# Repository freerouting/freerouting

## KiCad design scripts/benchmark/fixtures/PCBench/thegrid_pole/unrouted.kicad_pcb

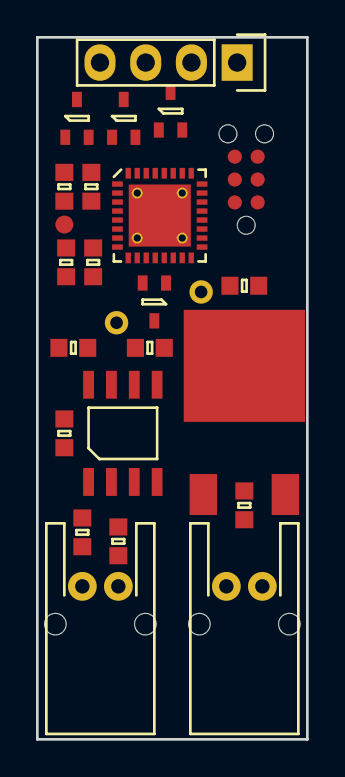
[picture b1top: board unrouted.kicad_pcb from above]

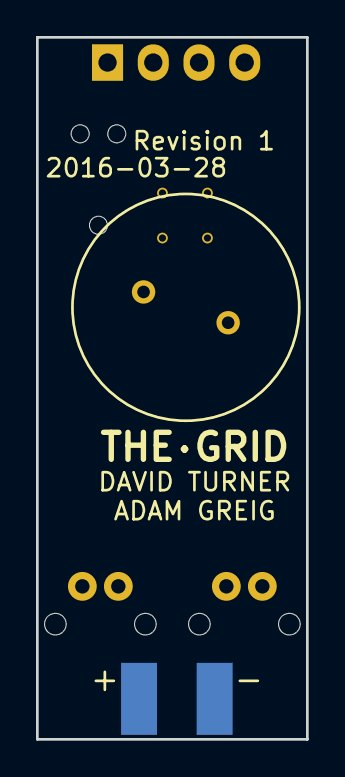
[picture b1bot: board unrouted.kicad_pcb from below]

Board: 2 copper layers, 15.0 x 39.0 mm, 25 parts (2 on the bottom side), 18 nets, no tracks yet.

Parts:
C1, C3, C5, C6: 100n; 0603
C2: 4u7; 0603
C4: 10n; 0603
C7: 10u; 0603
C8: 1u; 0603
IC1: LMx93; SOIC-8
IC2: STM32F0xxKxUx; QFN-32-EP-ST
P1: POWER_IN; minipow_edge
P2: BUS_IN; S02B-PASK-2
P3: BUS_OUT; S02B-PASK-2
P4: SWD_TC; TC2030-NL
P5: LEDs; Pin_Header_Straight_1x04
Q1, Q2, Q3, Q4: MTM232270LBF; SOT-323
R1, R2: 10k; 0603
R3: 1M; 0603
SP1: SPEAKER; piezo
TP1: RST; TESTPAD
U1: LD1117S33TR; TO-252-3

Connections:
+3V3: C1.2, C2.1, C3.1, C4.1, C5.1, C7.1, C8.1, IC1.8, IC2.1, IC2.5, IC2.17, P4.1, R1.1, U1.2
+12V: C6.1, P1.2, P5.1, SP1.1, U1.3
/BUS: IC1.1, IC2.9, R1.2, R3.1
/BUS_A: IC1.2, P2.1, P3.1
/BUS_B: P2.2, P3.2, R2.2
/DRIVE_B: P5.4, Q3.3
/DRIVE_G: P5.3, Q2.3
/DRIVE_R: P5.2, Q1.3
/LED_B: IC2.20, Q3.1
/LED_G: IC2.19, Q2.1
/LED_R: IC2.18, Q1.1
/PIEZO: IC2.10, Q4.1
/SWDCLK: IC2.24, P4.4
/SWDIO: IC2.23, P4.2
GND: C1.1, C2.2, C3.2, C4.2, C5.2, C6.2, C7.2, C8.2, IC1.4, IC1.5, IC1.6, IC2.31, IC2.EP, P1.1, P4.5, Q1.2, Q2.2, Q3.2, Q4.2, U1.1
unnamed: IC1.3, R2.1, R3.2
unnamed: IC2.4, TP1.1
unnamed: Q4.3, SP1.2

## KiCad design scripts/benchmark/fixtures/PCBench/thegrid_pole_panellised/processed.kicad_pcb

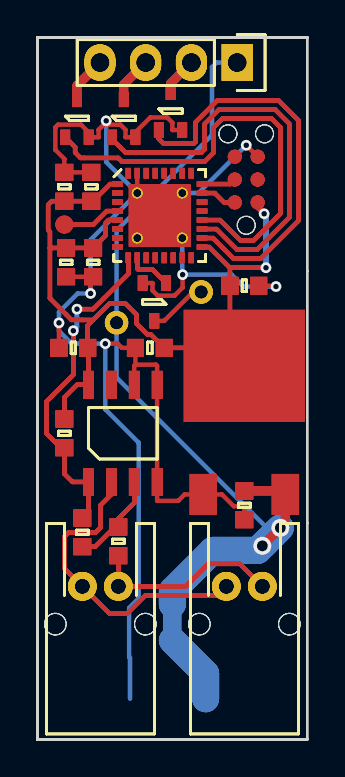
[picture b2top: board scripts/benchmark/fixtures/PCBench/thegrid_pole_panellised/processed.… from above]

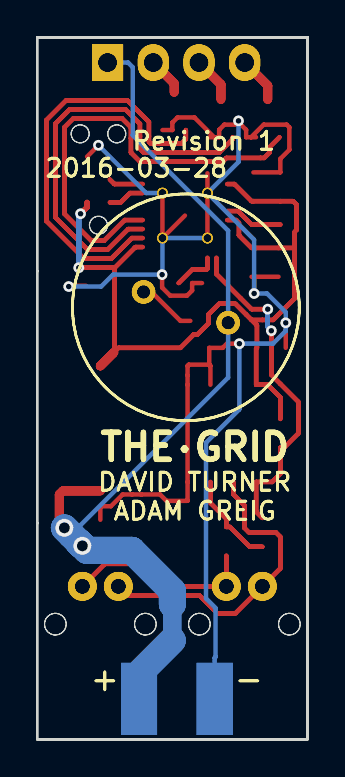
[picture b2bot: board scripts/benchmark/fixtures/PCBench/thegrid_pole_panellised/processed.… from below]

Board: 2 copper layers, 15.0 x 39.0 mm, 50 parts (4 on the bottom side), 18 nets.

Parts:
C1, C1_2, C3, C3_2, C5, C5_2, C6, C6_2: 100n; 0603
C2, C2_2: 4u7; 0603
C4, C4_2: 10n; 0603
C7, C7_2: 10u; 0603
C8, C8_2: 1u; 0603
IC1, IC1_2: LMx93; SOIC-8
IC2, IC2_2: STM32F0xxKxUx; QFN-32-EP-ST
P1, P1_2: POWER_IN; minipow_edge
P2, P2_2: BUS_IN; S02B-PASK-2
P3, P3_2: BUS_OUT; S02B-PASK-2
P4, P4_2: SWD_TC; TC2030-NL
P5, P5_2: LEDs; Pin_Header_Straight_1x04
Q1, Q1_2, Q2, Q2_2, Q3, Q3_2, Q4, Q4_2: MTM232270LBF; SOT-323
R1, R1_2, R2, R2_2: 10k; 0603
R3, R3_2: 1M; 0603
SP1, SP1_2: SPEAKER; piezo
TP1, TP1_2: RST; TESTPAD
U1, U1_2: LD1117S33TR; TO-252-3

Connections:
+3V3: C1.2, C1_2.2, C2.1, C2_2.1, C3.1, C3_2.1, C4.1, C4_2.1, C5.1, C5_2.1, C7.1, C7_2.1, C8.1, C8_2.1, IC1.8, IC1_2.8, IC2.1, IC2.5, IC2.17, IC2_2.1, IC2_2.5, IC2_2.17, P4.1, P4_2.1, R1.1, R1_2.1, U1.2, U1_2.2
+12V: C6.1, C6_2.1, P1.2, P1_2.2, P5.1, P5_2.1, SP1.1, SP1_2.1, U1.3, U1_2.3
/BUS: IC1.1, IC1_2.1, IC2.9, IC2_2.9, R1.2, R1_2.2, R3.1, R3_2.1
/BUS_A: IC1.2, IC1_2.2, P2.1, P2_2.1, P3.1, P3_2.1
/BUS_B: P2.2, P2_2.2, P3.2, P3_2.2, R2.2, R2_2.2
/DRIVE_B: P5.4, P5_2.4, Q3.3, Q3_2.3
/DRIVE_G: P5.3, P5_2.3, Q2.3, Q2_2.3
/DRIVE_R: P5.2, P5_2.2, Q1.3, Q1_2.3
/LED_B: IC2.20, IC2_2.20, Q3.1, Q3_2.1
/LED_G: IC2.19, IC2_2.19, Q2.1, Q2_2.1
/LED_R: IC2.18, IC2_2.18, Q1.1, Q1_2.1
/PIEZO: IC2.10, IC2_2.10, Q4.1, Q4_2.1
/SWDCLK: IC2.24, IC2_2.24, P4.4, P4_2.4
/SWDIO: IC2.23, IC2_2.23, P4.2, P4_2.2
GND: C1.1, C1_2.1, C2.2, C2_2.2, C3.2, C3_2.2, C4.2, C4_2.2, C5.2, C5_2.2, C6.2, C6_2.2, C7.2, C7_2.2, C8.2, C8_2.2, IC1.4, IC1.5, IC1.6, IC1_2.4, IC1_2.5, IC1_2.6, IC2.31, IC2.EP, IC2_2.31, IC2_2.EP, P1.1, P1_2.1, P4.5, P4_2.5, Q1.2, Q1_2.2, Q2.2, Q2_2.2, Q3.2, Q3_2.2, Q4.2, Q4_2.2, U1.1, U1_2.1
unnamed: IC1.3, IC1_2.3, R2.1, R2_2.1, R3.2, R3_2.2
unnamed: IC2.4, IC2_2.4, TP1.1, TP1_2.1
unnamed: Q4.3, Q4_2.3, SP1.2, SP1_2.2

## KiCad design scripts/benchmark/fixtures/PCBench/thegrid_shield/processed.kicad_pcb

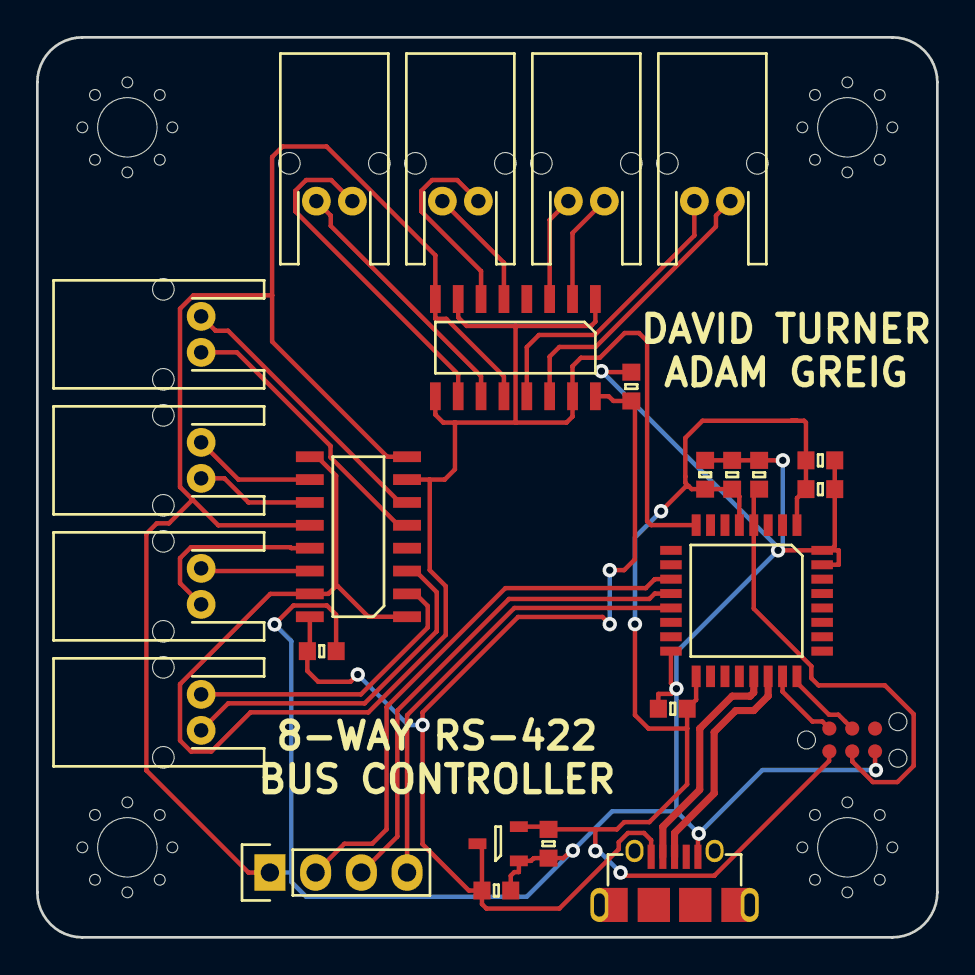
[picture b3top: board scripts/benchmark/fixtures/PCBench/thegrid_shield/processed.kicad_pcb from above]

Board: 2 copper layers, 50.0 x 50.0 mm, 29 parts (0 on the bottom side), 28 nets.

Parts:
C1, C2, C3, C6, C8: 100n; 0603
C4: 10u; 0603
C5: C; 0603
C7, C9, C10: 1u; 0603
IC1: STM32F0xxKxTx; LQFP-32
IC2: MCP1700; SOT-23
IC3, IC4: AM26C31; SOIC-16
J1: MICROUSB; MICROUSB_MOLEX_47589-0001
P1: SWD_TC; TC2030-NL
P5: SHIFT; Pin_Header_Straight_1x04
P6: BUS1; S02B-PASK-2
P7: BUS2; S02B-PASK-2
P8: BUS3; S02B-PASK-2
P9: BUS4; S02B-PASK-2
P10: BUS5; S02B-PASK-2
P11: BUS6; S02B-PASK-2
P12: BUS7; S02B-PASK-2
P13: BUS8; S02B-PASK-2
X1, X2, X3, X4: PART; M3_MOUNT

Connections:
+3V3: C3.1, C4.1, C6.1, C7.1, C8.1, C10.1, IC1.1, IC1.5, IC1.17, IC2.2, P1.1
+5V: C1.1, C2.1, C9.1, IC2.3, IC3.16, IC4.16, J1.1
/SHIFT_DATA: IC1.13, P5.4
/SHIFT_RCK: IC1.11, P5.2
/SHIFT_SRCK: IC1.12, P5.3
/SWDCLK: IC1.24, P1.4
/SWDIO: IC1.23, P1.2
/TX: IC1.8, IC3.1, IC3.7, IC3.9, IC3.15, IC4.1, IC4.7, IC4.9, IC4.15
/USB_D+: IC1.22, J1.3
/USB_D-: IC1.21, J1.2
/nRST: C5.1, IC1.4, P1.3
GND: C1.2, C2.2, C3.2, C4.2, C5.2, C6.2, C7.2, C8.2, C9.2, C10.2, IC1.16, IC1.31, IC1.32, IC2.1, IC3.8, IC3.12, IC4.8, IC4.12, J1.5, P1.5, P5.1
unnamed: IC3.2, P6.1
unnamed: IC3.3, P6.2
unnamed: IC3.5, P7.2
unnamed: IC3.6, P7.1
unnamed: IC3.10, P8.1
unnamed: IC3.11, P8.2
unnamed: IC3.13, P9.2
unnamed: IC3.14, P9.1
unnamed: IC4.2, P10.1
unnamed: IC4.3, P10.2
unnamed: IC4.5, P11.2
unnamed: IC4.6, P11.1
unnamed: IC4.10, P12.1
unnamed: IC4.11, P12.2
unnamed: IC4.13, P13.2
unnamed: IC4.14, P13.1

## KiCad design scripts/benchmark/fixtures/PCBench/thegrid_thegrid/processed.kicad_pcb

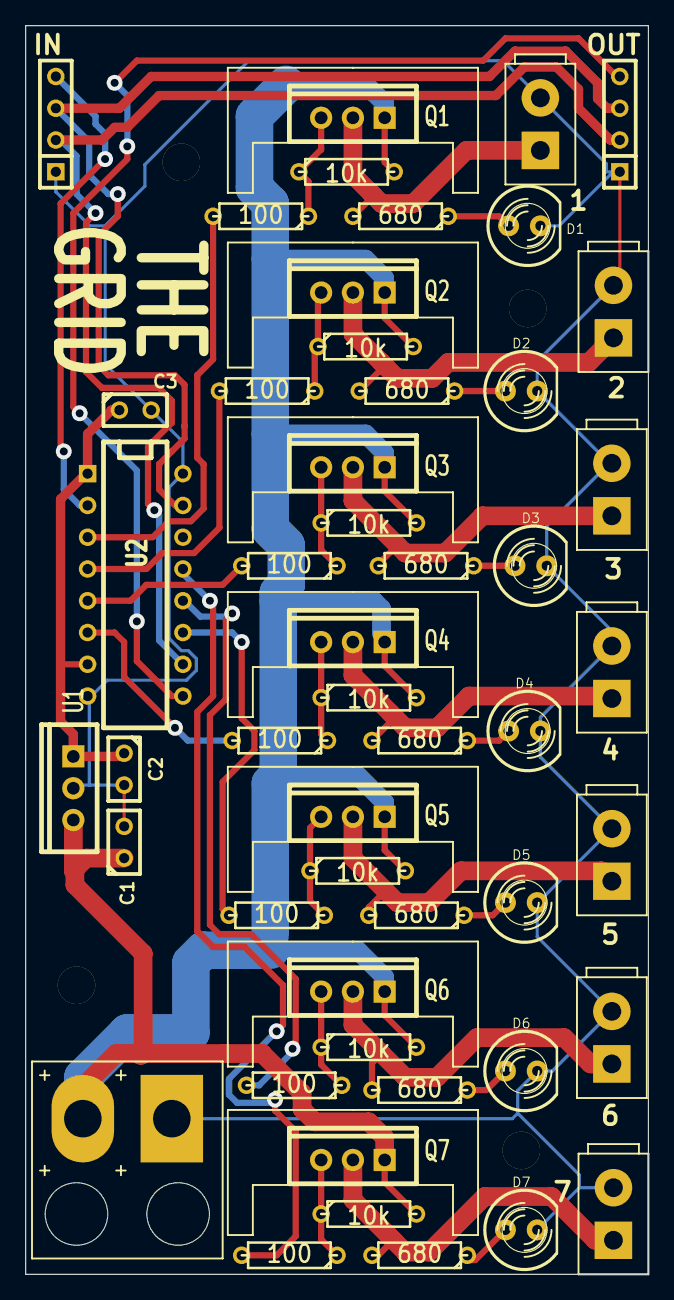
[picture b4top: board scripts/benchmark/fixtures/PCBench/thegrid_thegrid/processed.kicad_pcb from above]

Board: 2 copper layers, 49.8 x 99.8 mm, 54 parts (0 on the bottom side), 35 nets.

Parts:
C1: .33u; C1
C2: .1u; C1
C3: 100n; C1
D1, D2, D3, D4, D5, D6, D7: LED; LED-5MM
MH: MountingHole_3mm_RevA_Date21Jun2010; MountingHole_3mm
MH_2, MH_3, MH_4: MountingHole_3mm_RevA_Date21Jun2010; MountingHole_3mm
P1: POWER; SIL-2
P2: SHIFT_IN; SIL-4
P3: SHIFT_OUT; SIL-4
P4, P5, P6, P7, P8, P9, P10: CONN_2; SIL-2
Q1, Q2, Q3, Q4, Q5, Q6, Q7: FQP7P06; TO220_VERT
R1, R3, R5, R7, R9, R11, R13: 10k; R3
R2, R4, R6, R8, R10, R12, R14: 100; R3
R15, R16, R17, R18, R19, R20, R21: 680; R3
U1: UA7805CKCS; TO220_VERT
U2: TPIC6C595; DIP-16__300

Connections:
+5V: C2.1, C3.1, U1.1, U2.1, U2.7
+12V: C1.1, P1.2, Q1.1, Q2.1, Q3.1, Q4.1, Q5.1, Q6.1, Q7.1, R1.2, R3.2, R5.2, R7.2, R9.2, R11.2, R13.2, U1.2
GND: C1.2, C2.2, C3.2, D1.2, D2.2, D3.2, D4.2, D5.2, D6.2, D7.2, P1.1, P2.1, P3.1, P4.2, P5.2, P6.2, P7.2, P8.2, P9.2, P10.2, U1.3, U2.8, U2.16
unnamed: D1.1, R15.1
unnamed: D2.1, R16.1
unnamed: D3.1, R17.1
unnamed: D4.1, R18.1
unnamed: D5.1, R19.1
unnamed: D6.1, R20.1
unnamed: D7.1, R21.1
unnamed: P2.2, P3.2, U2.10
unnamed: P2.3, P3.3, U2.15
unnamed: P2.4, U2.2
unnamed: P3.4, U2.9
unnamed: P4.1, Q1.3, R15.2
unnamed: P5.1, Q2.3, R16.2
unnamed: P6.1, Q3.3, R17.2
unnamed: P7.1, Q4.3, R18.2
unnamed: P8.1, Q5.3, R19.2
unnamed: P9.1, Q6.3, R20.2
unnamed: P10.1, Q7.3, R21.2
unnamed: Q1.2, R1.1, R2.1
unnamed: Q2.2, R3.1, R4.1
unnamed: Q3.2, R5.1, R6.1
unnamed: Q4.2, R7.1, R8.1
unnamed: Q5.2, R13.1, R14.1
unnamed: Q6.2, R9.1, R10.1
unnamed: Q7.2, R11.1, R12.1
unnamed: R2.2, U2.3
unnamed: R4.2, U2.4
unnamed: R6.2, U2.5
unnamed: R8.2, U2.6
unnamed: R10.2, U2.12
unnamed: R12.2, U2.13
unnamed: R14.2, U2.11
